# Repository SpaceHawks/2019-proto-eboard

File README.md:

This repository contains the schematic and PCB for the 2019-2020 electrical board. For a walkthrough of this season's progress and an in-depth explanation of the system, see the IPRO report. For a quick glance at the schematic or boards, look in the [PDFs](/PDFs) folder. For information not printed on the schematic (e.g. datasheet links, trace widths), open the files in KiCad.

To view or edit these files, use KiCad version 5. You may need to [install the latest libraries](http://kicad.org/libraries/download/) if they don't come with your installation.

# Spring 2020: Electrical Team IPRO Report

Gabriel Krell

Gregory Bonnema

Jack Pio

## I. Electrical Team Goals

The NASA RMC at Illinois Tech electrical team's goal was a reliable, professional electrical system for our robot. To accomplish this, we needed to plan the system in a reasonable, realistic way, implement our plan with well-reviewed eCAD, and turn those schematics into a physical robot. This year the team wanted to keep the same topology as previous years, making incremental changes. We aimed to have capable microelectronics and robot control systems running on top of a safe and reliable power system. Our robot would need to adhere to minimum specifications set by the competition (e.g. “The robot should include an emergency stop”) and those set by our goal-planning activity (e.g. “The robot should move”). We also had a nonfunctional goal: to spend as little as reasonably possible, designing to reuse parts from last year and use new parts we had already had. Overall our aim was to continue the success of the past NASA RMC teams, while improving efficiency and overall performance, making it easier to work together with the other subteams.

## II. Power Electronics

Conceptually, we split the electrical design of the robot into two sections. The “power electronics” section was chiefly concerned with getting power from batteries to motors in a safe way.

### A. Initial Design

To lay out our plan for the power electronics section (and eventually make our final schematic), we started from a base of the previous year’s layout. Like other robotics competitions, the rules required an easy-to-reach emergency stop button (“E-stop”). We were also required to measure and display the total power consumed by the robot. On top of these mandatory elements, the relevant section of last year’s robot included:

- A single 3S hobby LiPo battery to power the robot

- A resettable circuit breaker to protect against sustained overcurrent

- A “remote E-stop” (actually a remote-controlled relay unit)

- A smaller, light-up power switch

- A solid-state relay (SSR) to toggle power to the robot

- Sabertooth 2x60 motor controllers to actually move the motors

- A panel-mount battery voltage display

We thought that this layout was simple to implement and was reasonably safe. We were able to build it using only parts that we already possessed from last year’s competition. However, we were concerned that the circuit breaker would take too long to open (10-25 seconds) during a projected overcurrent condition or short circuit. We investigated several options for faster responses: active control with a MOSFET, fast-blow fuses, and different circuit breakers. Unfortunately, breakers or fuses with our desired response characteristics were prohibitively expensive, and our subteam didn’t have the resources to implement active current protection. Ultimately, we compromised by including additional protection for the delicate microelectronics and trusting in the builtin current limiting on individual Sabertooths. Of course, we want to prevent any possible damage to the robot, but since this system includes a working E-stop and does not pose a fire hazard, it meets the relevant safety requirements.

### B. Modifications

We assembled a prototype electrical board as a proof-of-concept and began testing. We found that when motors were stalled, the high current draw would result in significant voltage drops across wires and especially across the SSR. This lowered the available voltage to below that required by the 12V-5V DC-DC converter, resulting in brownouts. We added a second SSR so that the microelectronics would not be affected by the high voltage drop across the SSR. We soon realized, however, that the high current was also causing the battery’s voltage to sag to unacceptable levels. To fix the problem, we added a second battery that would not be responsible for providing high current to the motors. This is not a perfect solution, because it required additional parts and weight, but it would perform well with the supplies on hand.

### C. Motor control

Like last year, we used Sabertooth 2x60 motor controllers. Each channel can supply up to 60A continuous or 120A peak; the Sabertooths are controlled via analog input, an R/C receiver, or serial input. Unfortunately, the controllers return no information about motor output or power consumption. To implement closed-loop control, we added output sensing for all motors: circuits to read the built-in potentiometers on the linear actuators, current sensing resistors on all motors, and a rotary encoder on the most critical motor.

## III. Microelectronics

The second section of the robot’s electronics system was responsible for sensor inputs, computation, and output signals. From the outset, we planned to use a PCB for reliable functionality in a small form factor.

The robot would be run by a single-board computer (SBC). The SBC would sense the outside world through an IMU and two LIDAR sensors, monitor the robot with current and position sensors, and output commands to the motor controllers. We initially used an ASUS Tinker Board, which we exchanged for a more powerful Raspberry Pi 3B+ at the request of the Programming Department.

### A. IMU

We included an inertial measurement unit (IMU) that would report the robot’s velocity and position in space. Because we already had a breakout board from Sparkfun, and because good libraries are available for it, we chose the MPU-6050 for our IMU. The MPU-6050 communicates with the SBC via I2C, a relatively slow multi-device protocol which is easy to connect and route on a circuit board. Sparkfun publishes schematics and board files for their hardware, so we included both the MPU-6050 circuit and headers to connect to the breakout. This way, we could use the expensive breakout board in our first PCB, but use the bare chip if a second version of the PCB forced us to order components.

### B. Potentiometer ADC

The robot incorporates three linear actuators and a four-wire servo to move the regolith collection system and sense how much icy regolith has been collected. All three linear actuators and the servo have built-in potentiometers for position sensing. Because our SBC was not able to read analog inputs by itself, we included an ADC to measure these voltages. We chose the ADS1015, an inexpensive 12-bit ADC that connects to the same I2C bus already used for the IMU. Adafruit sells an ADS1015 breakout board commonly used as an ADC for Raspberry Pis, so the Programming team would enjoy easy-to-use libraries to interface with the chip. Throughout the component selection process, we worked closely with Programming to make sure they would have drivers and libraries to interface with the hardware we chose.

### C. Current Sensing

After struggling with brownouts caused by excessive power consumption by the motors, we became concerned with monitoring motor current. The competition scoring penalized high power usage, but not enough for points to be our motivation. Rather, we wanted the robot to be able to detect when a motor was stalled (high current) or disconnected (no current despite a command to move). This would allow us to prevent system instability caused by current spikes, to improve navigation with this extra information about the robot’s movement, and to increase our eventual competition score.

We measured the voltage across very small (.25mΩ) shunt resistors to calculate the current going through each motor. Two leads from each resistor went to a differential current sense amplifier, which amplified the small bipolar voltage difference into a unipolar voltage high enough to be accurately measured by a fast ADC.

This was probably the most technically difficult part of the project. As the motors spin forwards or backwards, the motor controllers output 12V/0V or 0V/12V on the two leads (referenced to the negative lead of the battery). This means that a shunt resistor on either side will sometimes be at 12V potential, so a “high-side” current measurement system is necessary. Typical ADCs are damaged by inputs higher than their supply voltage (usually 3.3V or 5V), so we had to use a specialized IC to make a high-side differential measurement.

We also needed to amplify this measurement. To avoid large power losses in the resistors, we needed to keep the voltage drop across them as low as possible. To limit resistor consumption to 1W at the max motor current of 60A, we could only allow a voltage drop of 15mV. An ADC’s resolution is evenly distributed over its entire input range, so a 12-bit 3.3V ADC would only have 18 values to choose from to represent current of 0-60A. Amplifying this value before it went into the ADC allowed us to have more precise current measurements.

Finally, we needed to filter the amplified output of the differential measurement. The Sabertooth 2x60 modulates motor power with PWM at 24kHz. The ADC we chose had a maximum sample rate of 75k sps across all 8 channels, well below the Nyquist rate of the signal. Even if we were using a faster ADC, we didn’t want our software to process 384,000 samples per second, which would consume valuable system resources. Instead, we used an RC filter with a cut-off frequency of around 160Hz. This would smooth high-frequency PWM while giving us an accurate picture of changes in motor current. We considered using a Butterworth-response Sallen-Key filter, which has a much sharper cutoff of high frequencies and is easy to implement. But because we needed eight of these filters in limited board space and budget, we went with the RC filter.

## IV. Implementation

Implementation of our design was split into three parts: schematic capture, PCB design, and physical layout of large parts on the robot. We used KiCad for all our eCAD, and tracked versions with GitHub so that everyone was able to see the most up-to-date files.

### A. Schematic

We began with a rough schematic focusing on the power electronics. We updated the schematic as we figured out how last year’s robot worked and made our own design changes. Having a reference design helped us quickly build the electrical system for a prototype robot, allowing us to verify the design and let Programming test out their code on real hardware. The prototype bot was invaluable for debugging the brownout problems mentioned in Section II-C. Work on the physical prototype and the schematic proceeded in tandem. Once we had implemented the microelectronics section on perfboard and verified motor control functionality, we were ready to design the PCB. At the same time, we knew that our well-tested power electronics section was unlikely to change, so we began planning the physical layout of the large parts on our robot.

### B. PCB

The PCB was designed over the course of several weeks, with an eye towards a small form factor and easy testability. To save space, we designed the board to stack on top of the SBC, and we included test points for the inevitable debugging sessions later on. After an initial online review, we ordered and tested the first version of the board. This version correctly supported motor control and the IMU, but we quickly realized that unlike the previous year’s Arduino, the Tinker Board does not have a built-in ADC. We had connected the built-in potentiometers of the linear actuators to GPIO pins that could only accept digital input. Luckily, we had scheduled plenty of time for a possible second PCB. We added the necessary ADC, along with some quality-of-life changes and the current sensing detailed in III-C, and ordered a second board.

### C. Physical Layout

With the designs of the PCB and schematic finalized, all that remained was the problem of how to apply these designs onto the robot itself. Given the extremely fine dust present in the competition, we decided to enclose the electrical system in a polycarbonate “e-box”. Our design was sealed with silicone caulk and included a removable front panel which slid on a set of rails. Although not entirely airtight, the box was designed to protect components from major dust contamination. We used weather-resistant panel-mount ports to connect the e-box with the motors, sensors, and emergency stop located elsewhere on the robot.

Our available space was scarcely larger than the total volume of the components, so we made careful mockups of different layouts to come up with a good arrangement. To save space, we stacked pairs of motor controllers, and stacked the PCB on top of the Tinker Board. The rest of the e-box was laid out around these core components, keeping in mind the aforementioned consideration for difficulty of wiring.

## VI. Conclusion

Although this year’s competition was interrupted by the COVID-19 pandemic, we still accomplished many of our goals for the robot and laid a strong foundation for next year. We also explored several promising areas for innovation in next year’s competition.

We designed and implemented a working, safe power system for the robot. We were able to identify historical trouble spots: the datasheet for the SSRs specified a large heat sink, and no heat sink had ever been used. This year, we used advanced phase change composite (PCC) heat sinks donated by AllCell, a local battery manufacturer. The lightweight phase change material absorbs energy as it melts, but is held together by a graphite substrate. This improves the performance and lifetime of the SSRs without adding a prohibitive amount of weight to the robot.

We are also proud of our microelectronics system. Rigorous online review and a schedule that allowed us time for a second spin produced a high-quality board. We were able to catch small issues: for instance, our second version of the board added rounded edges, optional pull-up resistors, and connectors that make it impossible to accidentally connect electrically-incompatible components. The removal of extraneous parts and overall simplification of the system allowed us to make a much more compact system than previous years.

We also accomplished our goal of minimal spending. Historically, the Electrical department has been responsible for a significant portion of the team’s budget. Last year, we spent $3,075 on parts and tools. This year, we spent $410, $232 of which went to soldering stations (the team possessed a single pencil-style iron with a damaged tip). Throughout the season, we designed with price in mind, using cheap or already-owned components.

As of this report, the pandemic has prevented us from receiving components to assemble the PCB, but we are hopeful that the parts will arrive so we can assemble the board and allow Programming to remotely test their software. We are confident in this year’s design, and hope it to be a great stepping stone to the future of the Scarlet Spacehawks.

## VII. Resources

[Don’t Fear the Filter: Lowpass Edition - Elliot Williams for Hackaday](https://hackaday.com/2017/03/08/dont-fear-the-filter-lowpass-edition/)

[Filter Design in Thirty Seconds - Bruce Carter for TI](http://www.ti.com/lit/an/sloa093/sloa093.pdf)

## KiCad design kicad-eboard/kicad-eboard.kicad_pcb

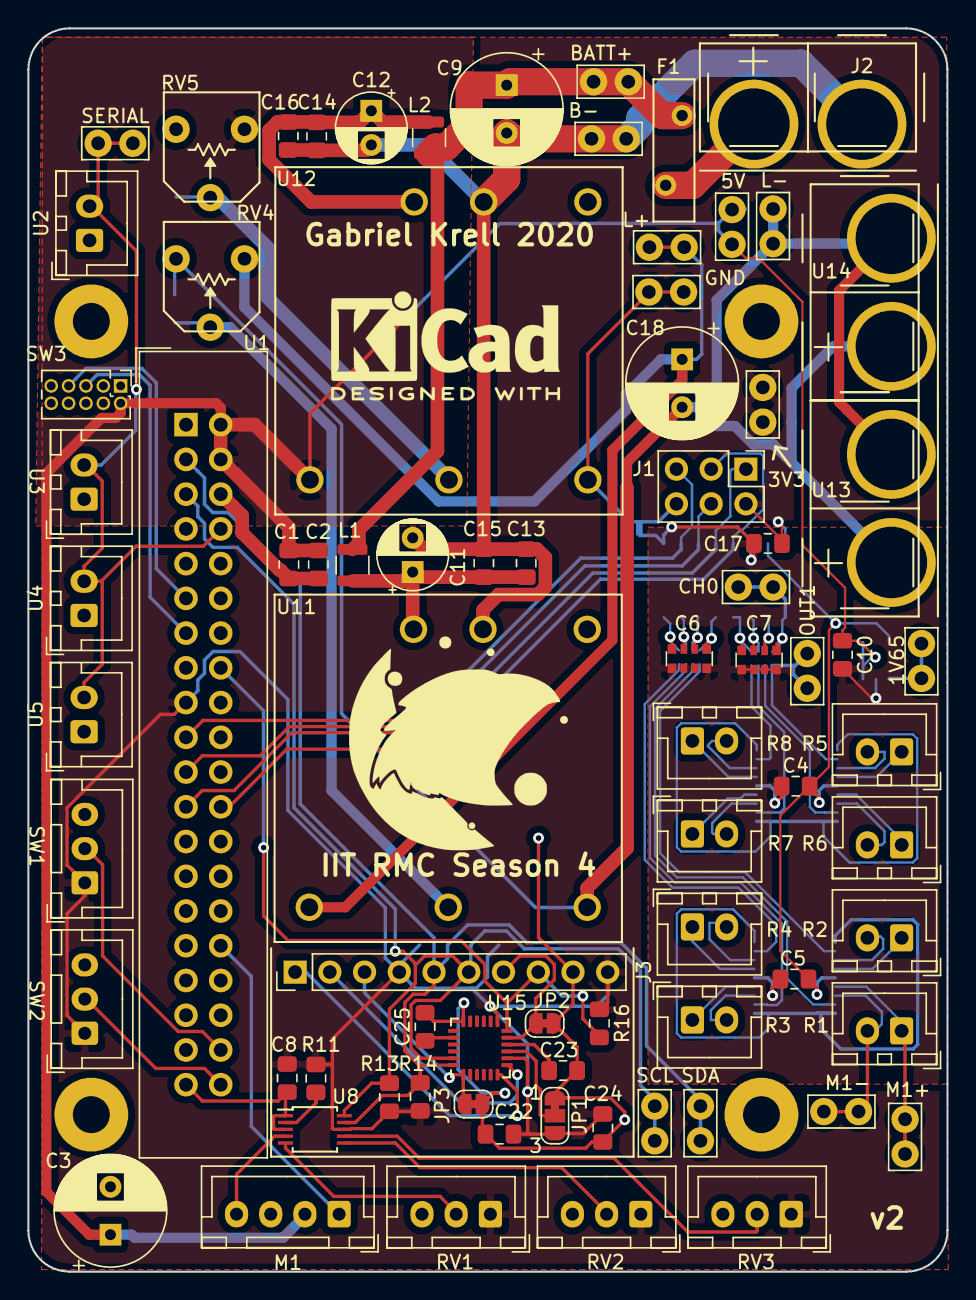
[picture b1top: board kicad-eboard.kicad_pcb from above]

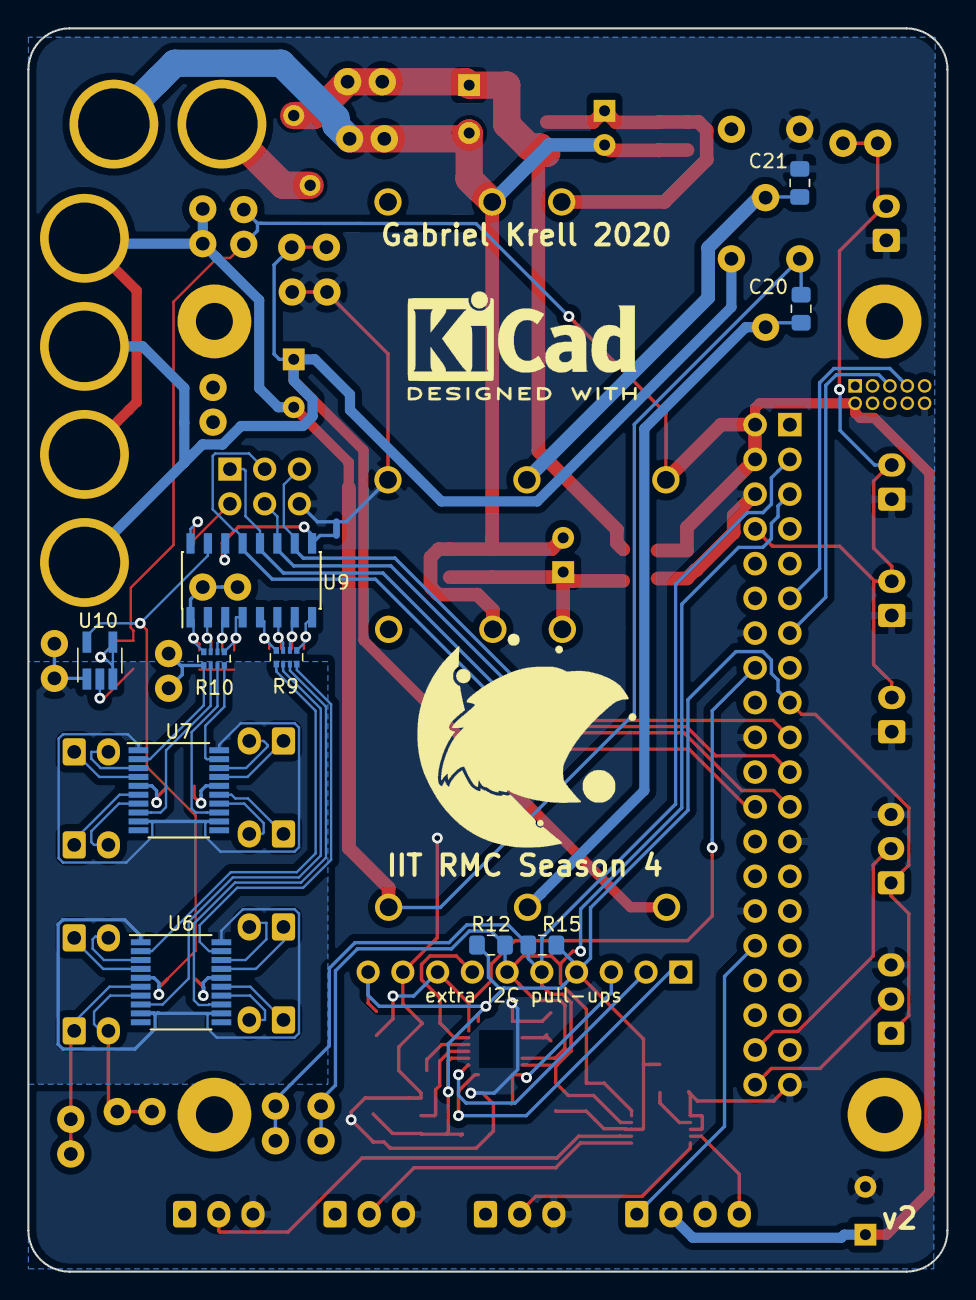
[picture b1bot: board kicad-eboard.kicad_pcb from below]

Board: 4 copper layers, 67.2 x 90.9 mm, 97 parts (13 on the bottom side), 72 nets.

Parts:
C1, C13, C14: 1u; C_0805_2012Metric_Pad1.15x1.40mm_HandSolder
C2, C15, C16, C20, C21, C22: 10n; C_0805_2012Metric_Pad1.15x1.40mm_HandSolder
C3, C18: 470u; CP_Radial_D8.0mm_P3.50mm
C4, C5, C8, C10, C17, C23, C24: 100n; C_0805_2012Metric_Pad1.15x1.40mm_HandSolder
C6, C7: 10n; C_Array_Convex_4x0612
C9: 1000u; CP_Radial_D8.0mm_P3.50mm
C11, C12: 100u; CP_Radial_D5.0mm_P2.50mm
C25: 2.2n; C_0805_2012Metric_Pad1.15x1.40mm_HandSolder
F1: 6A; Fuse_Littelfuse_16R600G
G1, G2: Logo; KiCad-Logo2_8mm_SilkScreen
G3, G4: Logo; SSH_logo
H1, H2, H3, H4: MountingHole; MountingHole_2.7mm_M2.5_Pad
J1: Conn_02x03; PinHeader_2x03_P2.54mm_Vertical
J2: Conn_01x02; Powerpole_45A_Vert_01x02_Holes
J3: Conn_01x10; PinHeader_1x10_P2.54mm_Vertical
JP1: SolderJumper_3_Bridged12; SolderJumper-3_P1.3mm_Bridged12_RoundedPad1.0x1.5mm_NumberL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
JP2, JP3: SolderJumper_2_Bridged; SolderJumper-2_P1.3mm_Bridged_RoundedPad1.0x1.5mm
L1, L2: 15u; L_1008_2520Metric
M1: Hopper_Servo; JST_XH_B4B-XH-A_1x04_P2.50mm_Vertical
NT1: Net-Tie_2; NetTie-2_SMD_Pad0.5mm
R1, R2, R3, R4, R5, R6, R7, R8: .25m; JST_XH_B2B-XH-A_1x02_P2.50mm_Vertical
R9, R10: 100k; R_Array_Convex_4x0402
R11, R12, R13, R14, R15, R16: 10k; R_0805_2012Metric_Pad1.15x1.40mm_HandSolder
RV1, RV2, RV3: 10k; JST_XH_B3B-XH-A_1x03_P2.50mm_Vertical
RV4, RV5: 10k; Potentiometer_Bourns_3306F
SW1: LIMIT_1; JST_XH_B3B-XH-A_1x03_P2.50mm_Vertical
SW2: LIMIT_2; JST_XH_B3B-XH-A_1x03_P2.50mm_Vertical
SW3: SRX_Encoder; PinHeader_2x05_P1.27mm_Vertical
TP1, TP2, TP3, TP4, TP5, TP6, TP7, TP8, TP9, TP10, TP11, TP12, TP13, TP14, TP15: TestPoint; TestPoint_Bridge_Pitch2.54mm_Drill1.0mm
U1: TinkerBoard; IDC-Header_2x20_P2.54mm_Vertical
U2, U3, U4, U5: Sabertooth2x60; JST_XH_B2B-XH-A_1x02_P2.50mm_Vertical
U6, U7: INA4181; TSSOP-20_4.4x6.5mm_P0.65mm
U8: ADS1015IDGS; TSSOP-10_3x3mm_P0.5mm
U9: MCP3008; SOIC-16_3.9x9.9mm_P1.27mm
U10: REF2033; SOT-23-5_HandSoldering
U11: PDQ15-Q24-S12-D; PDQXX-D_DC-DC_converter
U12: PDQ30-Q24-S5-D; PDQXX-D_DC-DC_converter
U13, U14: Hokuyo_UST-10LX; Powerpole_45A_Vert_01x02_Holes
U15: MPU-6050; InvenSense_QFN-24_4x4mm_P0.5mm

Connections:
+1.65V: TP10.1, U6.1, U6.9, U6.12, U6.20, U7.1, U7.9, U7.12, U7.20, U10.1
+3.3VADC: C4.1, C5.1, U6.5, U7.5, U9.15, U10.5
+3V3: C8.1, C17.1, C22.1, C24.1, J1.2, J3.4, J3.10, JP1.3, R11.1, R12.2, R13.1, R14.1, R15.2, R16.1, RV1.1, RV2.1, RV3.1, SW1.1, SW2.1, TP15.1, U1.1, U1.17, U8.8, U9.16, U15.8, U15.13
+5V: C1.1, C2.1, C3.1, C10.1, M1.2, RV5.3, SW3.2, TP13.1, U1.2, U1.4, U10.3, U10.4, U12.3
+12V: C18.1, RV4.3, TP11.1, U11.3, U13.2, U14.2
+BATT: C9.1, F1.2, L1.1, L2.1, TP8.1
/ENC_A: SW3.7, U1.11
/ENC_B: SW3.5, U1.13
/IMU/ADO: JP1.2, U15.9
/IMU/AUX_SCL: J3.2, U15.7
/IMU/AUX_SDA: J3.1, U15.6
/IMU/CLKIN: J3.3, JP3.1, U15.1
/IMU/FSYNC: J3.7, JP2.1, U15.11
/IMU/INT: J3.8, R16.2, U1.16, U15.12
/M1+: R1.1, TP4.1, U6.6
/M1-: R1.2, TP7.1, U6.7
/M2+: R2.1, U6.4
/M2-: R2.2, U6.3
/M3+: R3.1, U6.15
/M3-: R3.2, U6.14
/M4+: R4.1, U6.17
/M4-: R4.2, U6.18
/M5+: R5.1, U7.4
/M5-: R5.2, U7.3
/M6+: R6.1, U7.6
/M6-: R6.2, U7.7
/M7+: R7.1, U7.15
/M7-: R7.2, U7.14
/M8+: R8.1, U7.17
/M8-: R8.2, U7.18
/MISO: J1.1, U1.21, U9.12
/MOSI: J1.4, U1.19, U9.11
/SCL: J3.6, R12.1, R13.2, TP6.1, U1.5, U8.10, U15.23
/SCLK: J1.3, U1.23, U9.13
/SDA: J3.5, R14.2, R15.1, TP5.1, U1.3, U8.9, U15.24
/SS: J1.5, U1.24, U9.10
GND: C1.2, C2.2, C3.2, C8.2, C21.2, C22.2, C23.2, C24.2, C25.2, J1.6, J3.9, JP1.1, JP2.2, JP3.2, M1.3, NT1.2, RV1.3, RV2.3, RV3.3, RV5.1, SW1.3, SW2.3, SW3.10, TP14.1, U1.6, U1.9, U1.14, U1.20, U1.25, U1.30, U1.34, U1.39, U2.1, U3.1, U4.1, U5.1, U8.1, U8.3, U12.5, U15.18
GNDA: C18.2, C20.2, RV4.1, TP12.1, U11.5, U13.1, U14.1
GNDPWR: C9.2, C11.2, C12.2, C13.2, C14.2, C15.2, C16.2, J2.1, TP9.1, U11.2, U12.2
GNDREF: C4.2, C5.2, C6.5, C6.6, C6.7, C6.8, C7.5, C7.6, C7.7, C7.8, C10.2, C17.2, NT1.1, U6.16, U7.16, U9.9, U9.14, U10.2
unnamed: C6.1, R9.8, U9.5
unnamed: C6.2, R9.7, U9.6
unnamed: C6.3, R9.6, U9.7
unnamed: C6.4, R9.5, U9.8
unnamed: C7.1, R10.8, TP3.1, U9.1
unnamed: C7.2, R10.7, U9.2
unnamed: C7.3, R10.6, U9.3
unnamed: C7.4, R10.5, U9.4
unnamed: C11.1, C13.1, C15.1, L1.2, U11.1
unnamed: C12.1, C14.1, C16.1, L2.2, U12.1
unnamed: C20.1, RV4.2, U11.4
unnamed: C21.1, RV5.2, U12.4
unnamed: C23.1, U15.10
unnamed: C25.1, U15.20
unnamed: F1.1, J2.2
unnamed: M1.1, U1.32
unnamed: M1.4, U8.4
unnamed: R9.1, U6.2
unnamed: R9.2, U6.8
unnamed: R9.3, U6.13
unnamed: R9.4, U6.19
unnamed: R10.1, TP2.1, U7.2
unnamed: R10.2, U7.8
unnamed: R10.3, U7.13
unnamed: R10.4, U7.19
unnamed: R11.2, U8.2
unnamed: RV1.2, U8.5
unnamed: RV2.2, U8.6
unnamed: RV3.2, U8.7
unnamed: SW1.2, U1.38
unnamed: SW2.2, U1.40
unnamed: TP1.1, U1.8, U2.2, U3.2, U4.2, U5.2

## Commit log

2019-09-29 Add blank project
2019-09-29 Add watt meter symbol
2019-09-29 Add initial SSR section
2019-09-29 Add Sabertooth symbol
2019-10-03 Add .gitignore
2019-10-03 Use relative path for library
2019-10-04 Add circuit breaker symbols
    These are taken from the Device library, but are a pain to use if your KiCad
    install doesn't come with the latest Device. Best practice is probably gonna
    be to copy in everything that's not like R, C, etc.
2019-10-04 Add PWM breakout board
2019-10-04 Add TinkerBoard symbol
2019-10-04 Add DC-DC converters
2019-10-04 Fill in some power topology
2019-10-04 Satisfy some ERC things
2019-10-04 Add input filtering, trim to DC-DCs
2019-10-04 Add TinkerBoard decoupling caps
2019-10-04 Update SSR
2019-10-04 Add IMU breakout board
2019-10-05 Add LIDAR x2
2019-10-05 6 sabertooths, 1 per motor, subsheets
2019-10-05 Add encoder symbol
2019-10-06 Update lib source?
2019-10-07 Add encoders to schematic
    Add an encoder to each Sabertooth. Encoders can't run on 3.3V but 5V will
    damage TinkerBoard, so level shifter (voltage divider) is required. Just
    gave up and used air wires.
    Shifted over this section of main schematic to make room.
2019-10-07 Add limit switches; annotate
2019-10-07 Actually annotate
2019-10-23 Add power to wireless relay, light-up switch
2019-10-30 Fix I2C->PWM power
2019-10-30 Two motors per Sabertooth; fix PWM inputs
2019-10-30 Add linear actuators
2019-10-30 MPU-6050 is 3V3, not 5V
2019-10-30 Scooch over battery ground
2019-10-30 Fix ERC errors (add some power flags)
2019-11-09 Use serial instead of analog Sabertooth ctrl
2019-11-09 Revise motor/actuator count
2019-11-09 Add circuit breaker name, datasheet
2019-11-10 Tweak DCDC converter text position
2019-11-10 Annotate, tweak positions
2019-11-10 Add weird Windows changes
2019-11-10 Add test points
2019-11-10 Use 91k resistors instead of two 47k to fit parts on hand
2019-11-10 Add some footprints
2019-11-10 Add footprints for DC-DC converters
2019-11-13 Add more test points, battary->PCB connector
2019-11-13 Move #s to actually work
2019-11-13 Remove unused pin6 on encoders
2019-11-13 Add initial PCB component placement
2019-11-22 Fix footprint
2019-11-22 More PCB positioning
2019-11-22 Do some routing
2019-11-24 More routing
2019-11-24 Add emergency cap on 5V area; more routing
2019-12-22 Scratch
2019-12-24 Add breakout option for MP6050
2019-12-24 Add MP6050 footprint
2019-12-25 Square-er layout
2019-12-25 Fix inductor footprint
2019-12-25 More positioning
2019-12-26 Remove inaccurate inductor model
2019-12-26 Finish arrangement, start routing
2019-12-27 Annotate mounting holes; rotate board to fit screen
2019-12-27 Route first F.CU traces; reorder some inputs
2019-12-27 B.Cu encoder routing
2019-12-27 Finish routing
2019-12-27 Rotate back
2019-12-27 Touch up silkscreen
2019-12-27 Fix inductor broken by merge?
2019-12-27 Fix broken 3v3 pour
2019-12-27 Add SSH logo; move vias to accomodate
2019-12-27 Tweak logo
2019-12-27 Add autograph B-)
2019-12-28 Add version number silkscreen
2019-12-28 Add orientation symbol to pots
2019-12-28 Add readable test point silkscreens
2019-12-28 Clean up perimeter silkscreen
2019-12-28 Add INT pull-up
    I put this inside the MP6050 instead of outside the module where it "should" go
    because there wasn't really room in the schematic to put it on the first sheet.
2019-12-29 Add emergency I2C resistors
    The sub-sheet has kind of fallen out of sync with the Sparkfun original; I
    probably should have put the new resistors on sheet 1
2019-12-29 Add caps to trimpots
2019-12-29 Fix some DRC problems
2019-12-29 Move silkscreen off vias
2019-12-29 Add edge cuts
2019-12-29 More fiddling for 4pcb
2019-12-30 Update to v1
    Not proto anymore
2019-12-31 Add v1 PDFs
2020-01-01 Add PDQXX 3D model
2020-01-15 update schematic sheet name
2020-01-24 Add ADC
2020-01-24 Remove extra sabertooth
2020-01-29 Update inductor footprint, positioning
2020-01-29 potentiometer update
2020-02-01 Add pot datasheet
2020-02-01 Add separate SSR for power
2020-02-01 Rename potentiometer, add 3d model
2020-02-01 Add Powerpole vertical pairs
2020-02-01 Use Powerpole footprints, resistor arrays
2020-02-08 Update resistor, cap footprints
2020-02-08 Make resistors 0805
2020-02-08 Add resistor datasheet
2020-02-11 Add second battery
2020-02-11 Rearrange for current sensing
2020-02-11 Add voltage ref
2020-02-11 Add current sense amps (not connected to anything)
2020-02-12 Redo INA4181, add MCP3008
2020-02-12 Add encoder, current filtering
2020-02-12 Add SPI connections?
2020-02-13 Add some test points
2020-02-15 Add battery link
2020-02-17 Remove unused encoder PWM
2020-02-17 Add servo, decoupling caps
2020-02-17 Scooch over LIDAR
2020-02-17 Add 1.65 TP
2020-02-17 Remove unused schematic symbols
2020-02-17 Separate analog/digital ground, Vref
2020-02-17 Fix INA4181 pin type
2020-02-17 Add footprints
2020-02-17 Change big cap footprint
2020-02-17 Add some example routing
2020-02-17 Add capacitor array symbol
2020-02-17 Add capacitor array footprint
2020-02-18 Add Tinker Board outline
2020-02-18 Some track routing exploration
2020-02-18 Tweaks, fix INA4181 bypass caps
2020-02-18 Tweaks for class
2020-02-19 Work from IPRO
2020-02-19 Remove lonely ground?
2020-02-19 Add PTC fuse
2020-02-20 Route differential pairs
2020-02-20 Current sense routing take 2
2020-02-20 Update pot SS, keepout based on model
2020-02-20 Swap M1,m2 current sense
2020-02-20 Routing taking shape
2020-02-20 Change pin for rPi v4 compatibility
2020-02-21 Start moving things in prep for layout
2020-02-21 Increase PTC current
2020-02-21 More routing, moving components
2020-02-21 Finish routing?
2020-02-22 Silkscreen cleanup
2020-02-22 Fix Powerpole 3D/connection issue; more silkscreen
2020-02-22 Fix test point labels (oops)
2020-02-22 Add logo symbols, standardize component values
    Added a hacky almost-invisible schematic symbol for graphics, because
    otherwise hitting "Update PCB from Schematic" will delete footprints
    that aren't in the schematic. Also standardized component values - prefer
    100n to 0.1u; prefer 100n to 100nF; prefer 100k to 100K.
2020-02-22 Add note by graphics symbols
2020-02-22 Length match current sense leads
2020-02-24 Fix some unconnected nets
2020-02-25 Powerpole slots -> holes :(
2020-03-08 Rescue split resistor
2020-03-08 Use rescued R symbol
2020-03-08 Rename everything from 2019->season4
2020-03-08 Add v2 PDFs
2020-04-14 Add IPRO report
    don't accept this PR yet - using the github web editor for markdown preview but haven't added images yet
2020-04-14 Add images?
2020-04-14 Fix images?
2020-04-14 Add PCB images
2020-04-14 Fix PCB images
2020-09-17 added date
2020-09-17 Revert "added date"
    This reverts commit 0cdd8ac6e1c1616e55c703b4a8624dca90b81dce.
2021-11-08 Update README.md
    https://forum.kicad.info/t/warning-avoid-all-links-to-kicad-pcb-org-use-kicad-org/31521
